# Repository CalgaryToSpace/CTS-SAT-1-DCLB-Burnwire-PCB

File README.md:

# CTS-SAT-1-DCLB-Burnwire-PCB
CTS-SAT-1 burnwire driver PCB for the Deployable Composite Lattice Boom (DCLB)

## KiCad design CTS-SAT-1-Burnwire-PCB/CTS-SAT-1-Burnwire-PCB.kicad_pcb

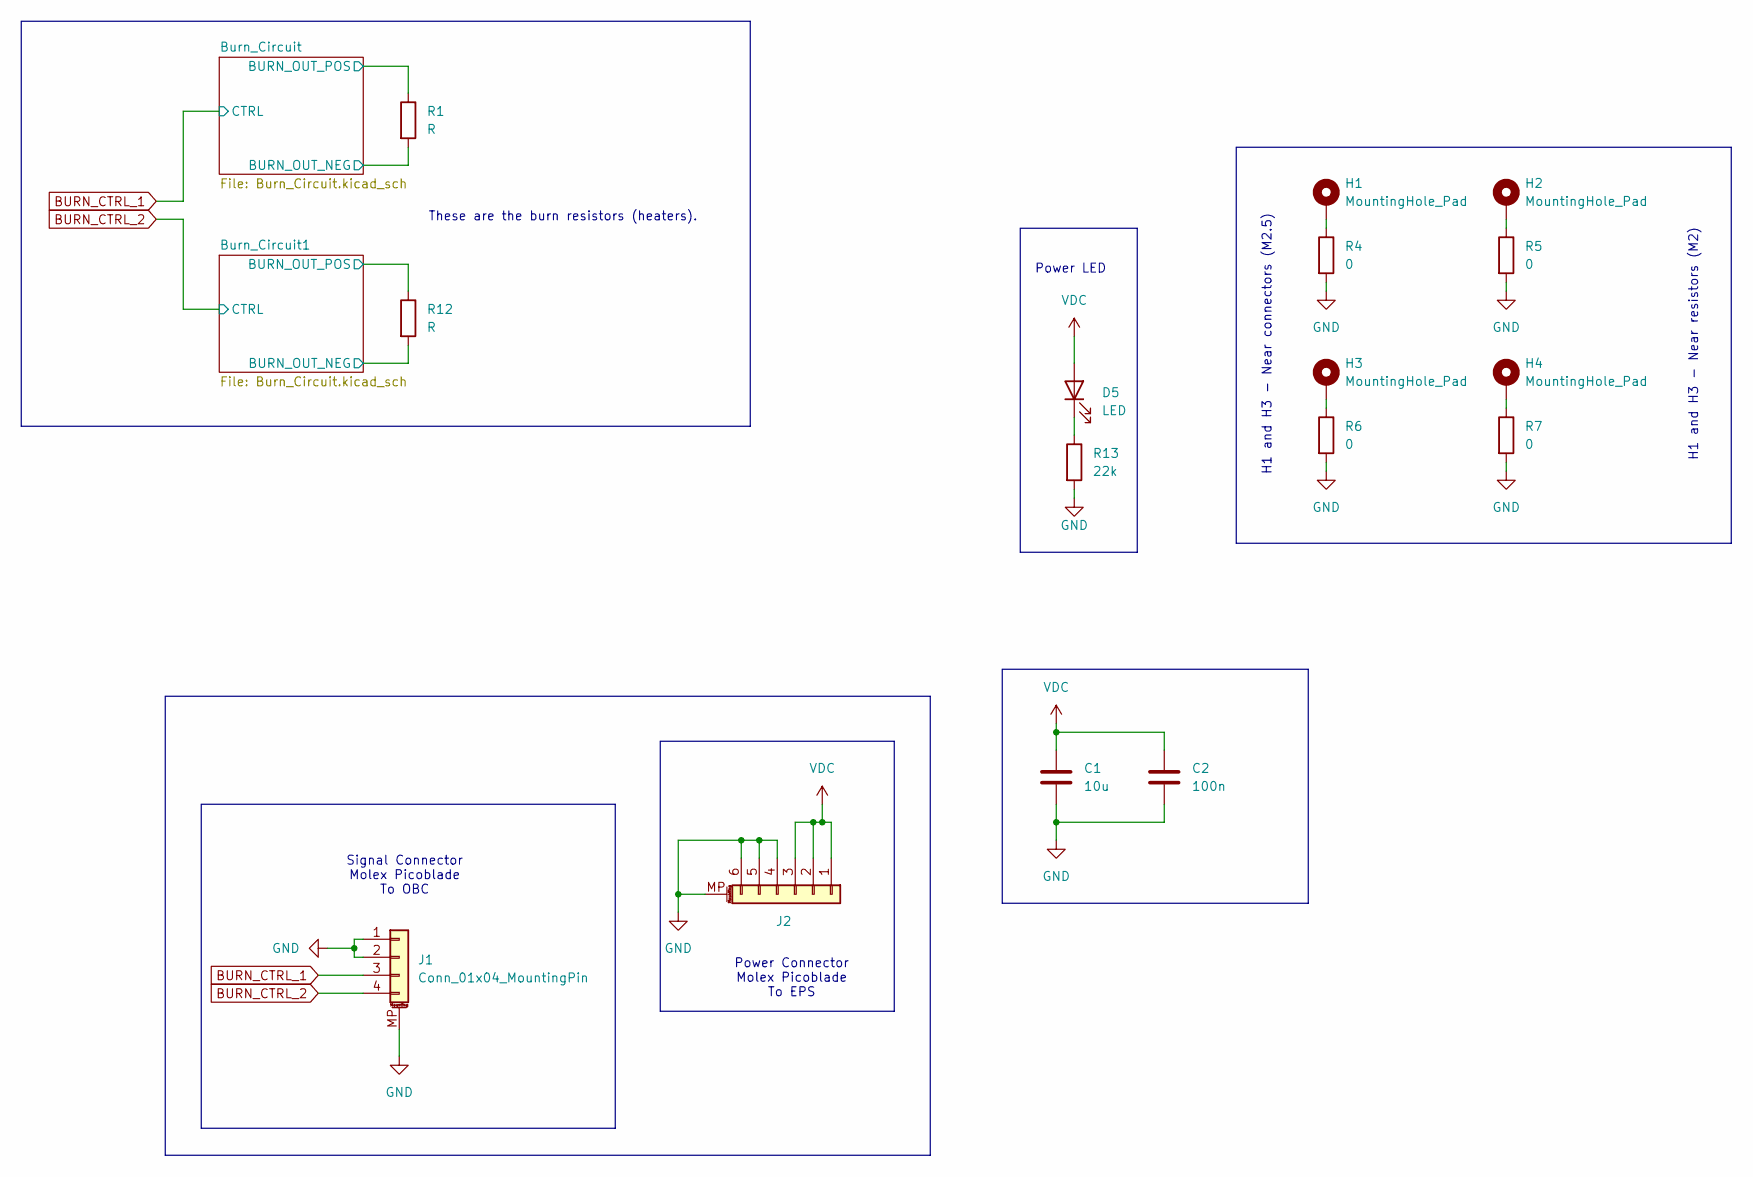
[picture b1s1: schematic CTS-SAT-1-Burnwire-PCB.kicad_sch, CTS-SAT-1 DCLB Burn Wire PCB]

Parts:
C1: 10u; C_1206_3216Metric_Pad1.33x1.80mm_HandSolder
C2: 100n; C_1206_3216Metric_Pad1.33x1.80mm_HandSolder
D5: LED; LED_0603_1608Metric_Pad1.05x0.95mm_HandSolder
H1, H3: MountingHole_Pad; MountingHole_2.7mm_M2.5_Pad
H2, H4: MountingHole_Pad; MountingHole_2.2mm_M2_Pad
J1: Conn_01x04_MountingPin; Molex_PicoBlade_53261-0471_1x04-1MP_P1.25mm_Horizontal
J2: Conn_01x06_MountingPin; Molex_PicoBlade_53261-0671_1x06-1MP_P1.25mm_Horizontal
R1: R; AxialBurnResistor
R4, R5, R6, R7: 0; R_0603_1608Metric_Pad0.98x0.95mm_HandSolder
R12: R; AxialBurnResistor_No_Cutout
R13: 22k; R_0603_1608Metric_Pad0.98x0.95mm_HandSolder

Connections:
/Burn_Circuit1/BURN_OUT_NEG: R12.2; also elsewhere on the board
/Burn_Circuit/BURN_OUT_NEG: R1.2; also elsewhere on the board
BURN_CTRL_1: J1.3; also elsewhere on the board
BURN_CTRL_2: J1.4; also elsewhere on the board
GND: C1.2, C2.2, J1.1, J1.2, J1.MP (MountPin), J2.4, J2.5, J2.6, J2.MP (MountPin), R4.2, R5.2, R6.2, R7.2, R13.2; also elsewhere on the board
unnamed: D5.1 (K), R13.1
unnamed: H1.1, R4.1
unnamed: H2.1, R5.1
unnamed: H3.1, R6.1
unnamed: H4.1, R7.1
VDC: C1.1, C2.1, D5.2 (A), J2.1, J2.2, J2.3, R1.1, R12.1; also elsewhere on the board

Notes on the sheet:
H1 and H3 - Near resistors (M2)
Power LED
H1 and H3 - Near connectors (M2.5)
Signal Connector Molex Picoblade To OBC
Power Connector Molex Picoblade To EPS
These are the burn resistors (heaters).

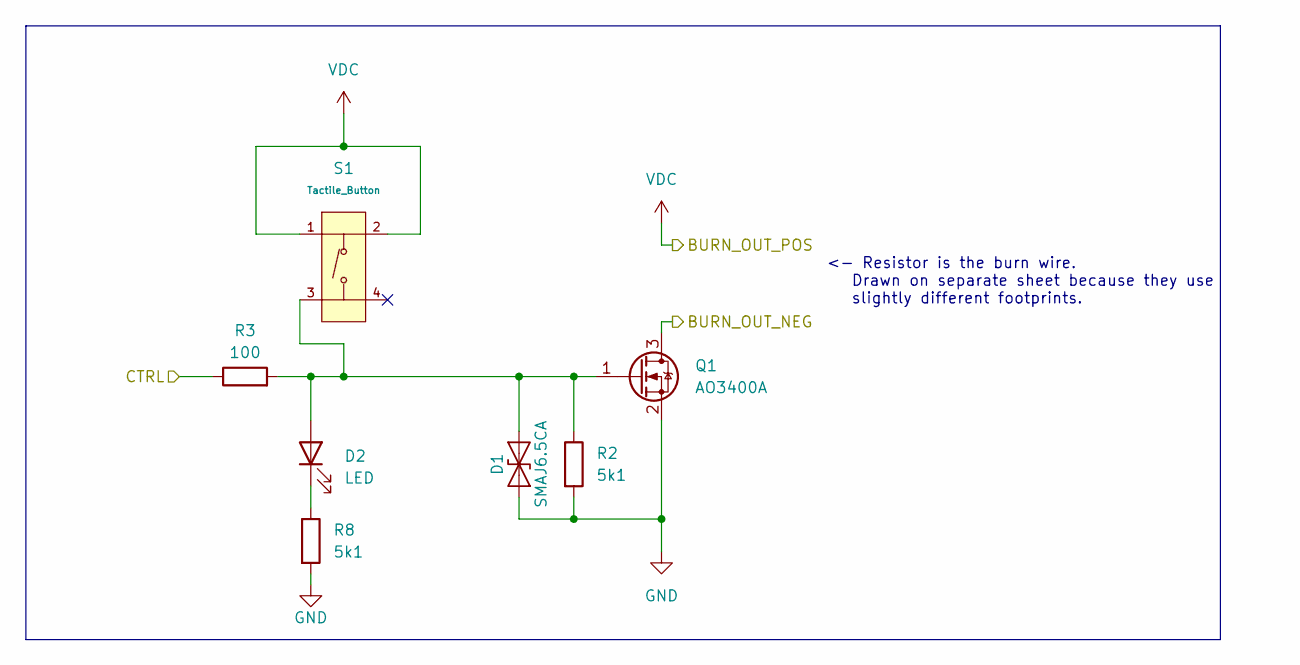
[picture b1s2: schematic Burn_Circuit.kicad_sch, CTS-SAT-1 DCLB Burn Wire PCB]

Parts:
D1: SMAJ6.5CA; D_SMA
D2: LED; LED_0603_1608Metric_Pad1.05x0.95mm_HandSolder
Q1: AO3400A; SOT-23_Handsoldering
R2, R8: 5k1; R_0603_1608Metric_Pad0.98x0.95mm_HandSolder
R3: 100; R_0603_1608Metric_Pad0.98x0.95mm_HandSolder
S1: Tactile_Button; SW-SMD_4P-L5.1-W5.1-P3.70-LS6.5-TL-2; Voltage Rating (Dc) 12V; Part TS-1187A-B-A-B; LCSC C318884

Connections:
/Burn_Circuit/BURN_OUT_NEG: Q1.3 (D); also elsewhere on the board
BURN_CTRL_1: R3.1; also elsewhere on the board
GND: D1.1 (A1), Q1.2 (S), R2.2, R8.2; also elsewhere on the board
unnamed: D1.2 (A2), D2.2 (A), Q1.1 (G), R2.1, R3.2, S1.3 (C)
unnamed: D2.1 (K), R8.1
VDC: S1.1 (A), S1.2 (B); also elsewhere on the board

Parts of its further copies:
D3: LED; LED_0603_1608Metric_Pad1.05x0.95mm_HandSolder
D4: SMAJ6.5CA; D_SMA
Q2: AO3400A; SOT-23_Handsoldering
R9: 100; R_0603_1608Metric_Pad0.98x0.95mm_HandSolder
R10, R11: 5k1; R_0603_1608Metric_Pad0.98x0.95mm_HandSolder
S2: Tactile_Button; SW-SMD_4P-L5.1-W5.1-P3.70-LS6.5-TL-2; Voltage Rating (Dc) 12V; Part TS-1187A-B-A-B; LCSC C318884

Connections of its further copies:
/Burn_Circuit1/BURN_OUT_NEG: Q2.3 (D); also elsewhere on the board
BURN_CTRL_2: R9.1; also elsewhere on the board
GND: D4.1 (A1), Q2.2 (S), R10.2, R11.2; also elsewhere on the board
unnamed: D3.2 (A), D4.2 (A2), Q2.1 (G), R9.2, R11.1, S2.3 (C)
unnamed: D3.1 (K), R10.1
VDC: S2.1 (A), S2.2 (B); also elsewhere on the board

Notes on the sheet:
<- Resistor is the burn wire. Drawn on separate sheet because they use slightly different footprints.

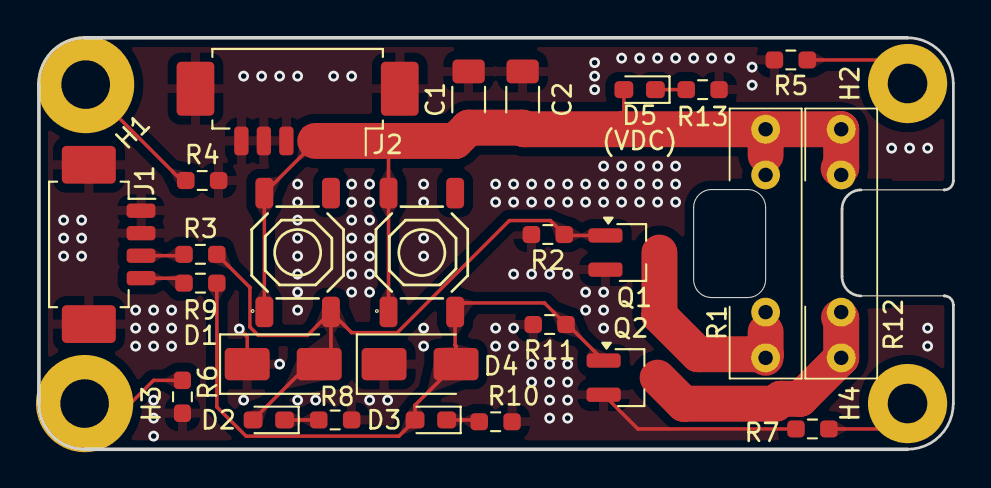
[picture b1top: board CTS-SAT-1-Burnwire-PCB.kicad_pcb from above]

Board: 2 copper layers, 50.8 x 22.9 mm, 30 parts (0 on the bottom side), 15 nets.

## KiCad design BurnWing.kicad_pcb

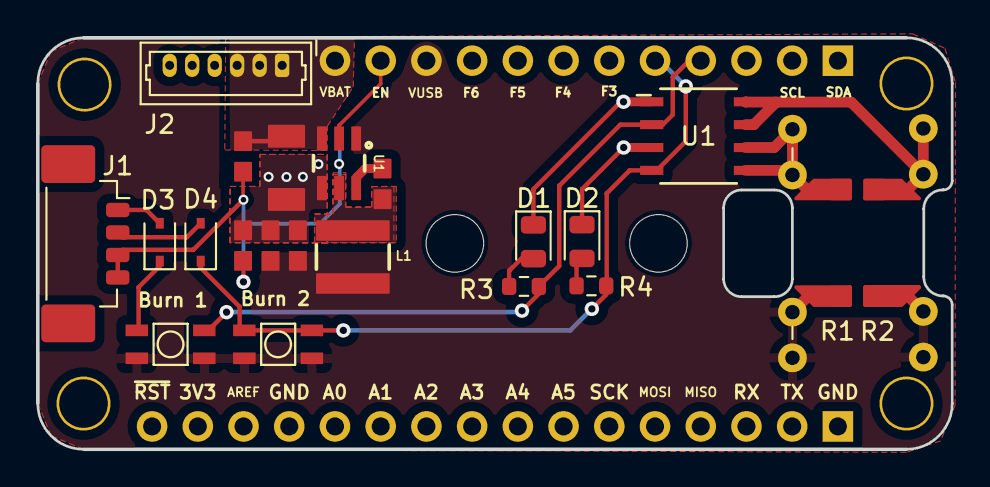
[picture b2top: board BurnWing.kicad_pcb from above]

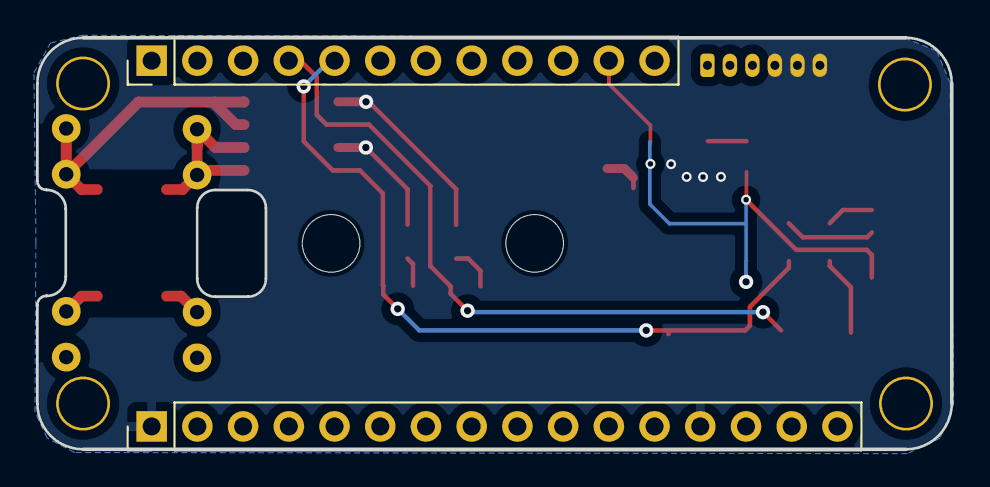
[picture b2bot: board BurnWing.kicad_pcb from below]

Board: 2 copper layers, 50.8 x 22.9 mm, 26 parts (2 on the bottom side), 8 nets.

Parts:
Burn 1, Burn 2: TACTILE_SWITCH_SMD
C1: 10uF; 1210
C2, C3: 0.1uF; 0603
C4: 22uF; 0603
D1: LED_RED_IN1; LED_0805_2012Metric
D2: LED_RED_IN2; LED_0805_2012Metric
D3, D4: D_Schottky_Small; D_SOD-323
J1: Molex_PicoBlade_53398-0471_1x04-1MP_P1.25mm_Verti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; Molex_PicoBlade_53398-0471_1x04-1MP_P1.25mm_Vertical
J2: Molex_PicoBlade_53047-0610_1x06_P1.25mm_Vertical
J3: feather long; PinHeader_1x16_P2.54mm_Vertical
J4: feather short; PinHeader_1x12_P2.54mm_Vertical
L1: 4.7uH; INDUCTOR_4X4MM
R1, R2#2: 100; R_Axial_DIN0207_L6.3mm_D2.5mm_P7.62mm_Horizontal
R1#2, R2#3: 100; R_2512_6332Metric
R1#3, R2: 100; 0603
R1#4: 100; R_Axial_DIN0309_L9.0mm_D3.2mm_P12.70mm_Horizontal
R3, R4: 10; R_0603_1608Metric
U1: BTS3405GXUMA1; SOT23-6
U1#2: BTS3405GXUMA1; PG-DSO-8-25_INF-L

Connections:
+5V: Burn 1.1, Burn 1.2, Burn 2.1, Burn 2.2, C3.1, C4.1, J4.10, L1.P$2, R1.2, R1#2.2, R1#4.2, R2#2.2, R2#3.2, U1.1 (SOURCE1)
EN3V: J1.3, J1.4, J4.11, R1#3.1, R2.2, U1.2 (IN1)
GND: C1.2, C3.2, C4.2, D1.1 (K), D2.1 (K), J2.4, J2.5, J2.6, J3.1, J3.13, R2.1, U1.4 (IN2), U1#2.1 (SOURCE1), U1#2.3 (SOURCE2)
IN1: Burn 1.3, Burn 1.4, D3.1 (K), D3.2 (A), J1.1, J4.4, R3.1, U1#2.2 (IN1)
IN2: Burn 2.3, Burn 2.4, D4.1 (K), D4.2 (A), J1.2, J4.5, R4.1, U1#2.4 (IN2)
unnamed: R1.1, R1#2.1, R1#4.1, U1#2.5 (DRAIN2), U1#2.6 (DRAIN2)
unnamed: R2#2.1, R2#3.1, U1#2.7 (DRAIN1), U1#2.8 (DRAIN1)
Vin: C2.2, J2.1, J2.2, J2.3, J4.12, L1.P$1, R1#3.2, U1.3 (SOURCE2), U1.5 (DRAIN2)

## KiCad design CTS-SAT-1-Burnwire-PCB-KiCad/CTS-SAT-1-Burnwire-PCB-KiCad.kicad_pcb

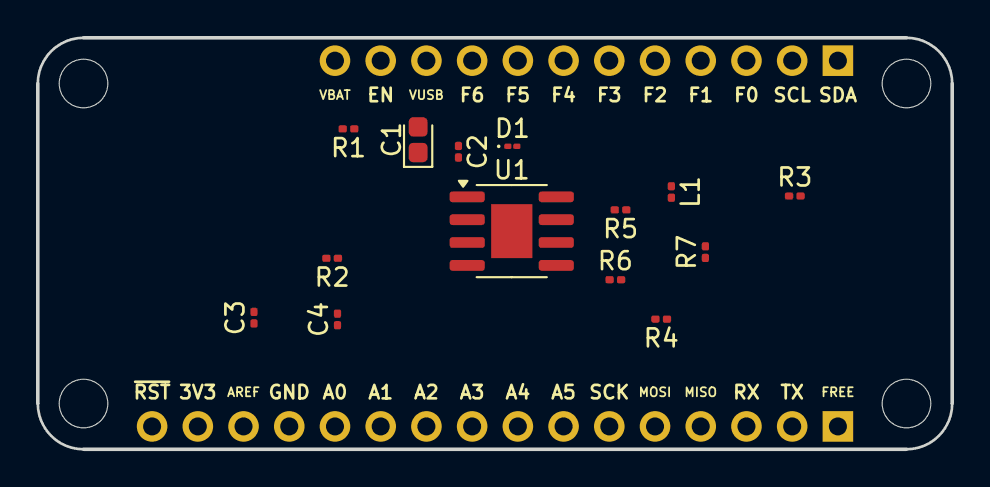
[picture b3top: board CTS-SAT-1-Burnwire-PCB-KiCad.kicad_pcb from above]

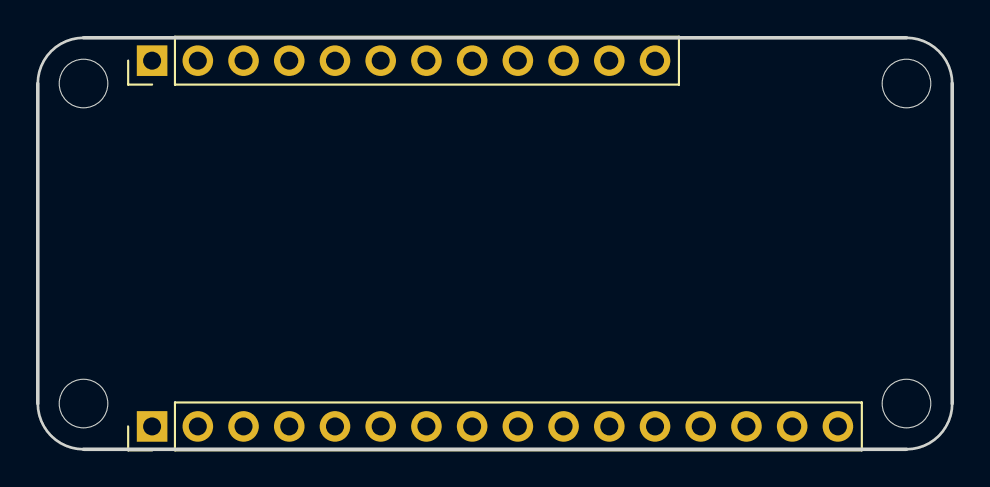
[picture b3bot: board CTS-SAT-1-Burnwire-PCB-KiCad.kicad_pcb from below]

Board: 2 copper layers, 50.8 x 22.9 mm, 16 parts (2 on the bottom side), 11 nets, no tracks yet.

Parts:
C1: 22µ; CP_EIA-1608-08_AVX-J
C2: 0.1µ; C_0201_0603Metric
C3, C4: 47µ; C_0201_0603Metric
D1: B540C; D_01005_0402Metric
J1: feather long; PinHeader_1x16_P2.54mm_Vertical
J2: feather short; PinHeader_1x12_P2.54mm_Vertical
L1: 2.5µ; L_0201_0603Metric
R1, R2, R5: 10.2k; R_0201_0603Metric
R3: 1.5; R_0201_0603Metric
R4: 33k; R_0201_0603Metric
R6: 10k; R_0201_0603Metric
R7: 0.5; R_0201_0603Metric
U1: ADP2303ARDZ; SOIC-8-1EP_3.9x4.9mm_P1.27mm_EP2.29x3mm

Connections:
EN3V: J2.11, R1.2, R2.2
GND: C3.2, C4.2, D1.1 (K), J1.13, R5.1, R7.2, U1.7 (GND), U1.9 (PADGND)
unnamed: C3.1, C4.1, L1.2, R3.2, R4.2
unnamed: C2.1, D1.2 (A), L1.1, U1.8 (SW)
unnamed: R3.1, R6.2, R7.1
unnamed: C2.2, U1.1 (BST)
unnamed: R1.1, U1.3 (EN)
unnamed: R4.1, R5.2, R6.1, U1.5 (FB)
unnamed: R2.1, U1.4 (PGOOD)
unnamed: C1.1, U1.2 (Vin)
Vin: C1.2, J2.12

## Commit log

2024-12-14 Add License - "CERN Open Hardware Licence Version 2 - Strongly Reciprocal"
2024-12-14 Update gitignore with KiCad 8
2024-12-14 Create Schematic for Burnwire
    Created burnwire circuit design inKicad
2024-12-18 Organized Schematic and PCB Layout
    Organized the Schematic to make it more neat and organized the ratsnest of the PCB.
2024-12-31 Low Side Switch Burnwire Design
    Added 350mA current limiting low side switch
    Added footprints for two thru-hole and two SMD burn resistors
    Added Picoblade connectors
    Added LEDs and test switches
2025-01-18 V3
    Updated layout/buck
2025-01-18 v3b
    Im bad at github
2025-01-24 Update README.md
    Added design doc link
2025-01-28 Update README.md
    typo fix
2025-02-01 Removed extra parts
    simplifed and cleaned things up a bit. Fixed schematic.
2025-02-01 folder fix
2025-02-04 Layout adjustments + added diodes
    Added some diodes to prevent backfeeding of test voltage.
    Routed remaining two picoblade pins to EN pin on buck reg.
2025-02-04 Added couple missing traces
    Added missing traces and updated pics/step
2025-02-08 Updated PCB design based on IC datasheet
    Took out extra resistors and adjusted current value to output the right current through the burn resistor.
2025-03-19 Remove work-in-progress designs - see other branch
2025-03-19 WIP: Create new empty PCB design with libraries
2025-03-19 Add board outline, connector locations
2025-03-19 Continue schematic design
2025-03-19 Layout and routing
2025-03-19 Convert to 2-resistor design
2025-03-19 Remove unnecessary vias
2025-03-19 Add logo, prep release
2025-05-06 Replace TVS diodes with SMAJ6.5CA
2025-05-06 Update mounting hole diameters
    M2 by the resistors and M2.5 by the connectors
2025-05-06 Add copper keepout under resistors
2025-05-09 Bump version number, add renders, clean up vias through silkscreens
2025-05-09 Add power indicator LED
2025-05-09 Add renders to README
2025-05-22 Update part numbers in schematic
